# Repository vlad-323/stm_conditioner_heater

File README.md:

# stm_conditioner_heater
 Прилад дозволяє керувати компресором, обігрівом компресора та обігрівом піддона.
 # Схема електрична принципова

 # Зовнішній вигляд приладу

 # Логіка роботи
 1. Ініціалізація усіх входів та виходів
 2. Якщо вхід компресора вимкнений -> компресор і ТЕН компресора вимкнені
 3. work in progress...

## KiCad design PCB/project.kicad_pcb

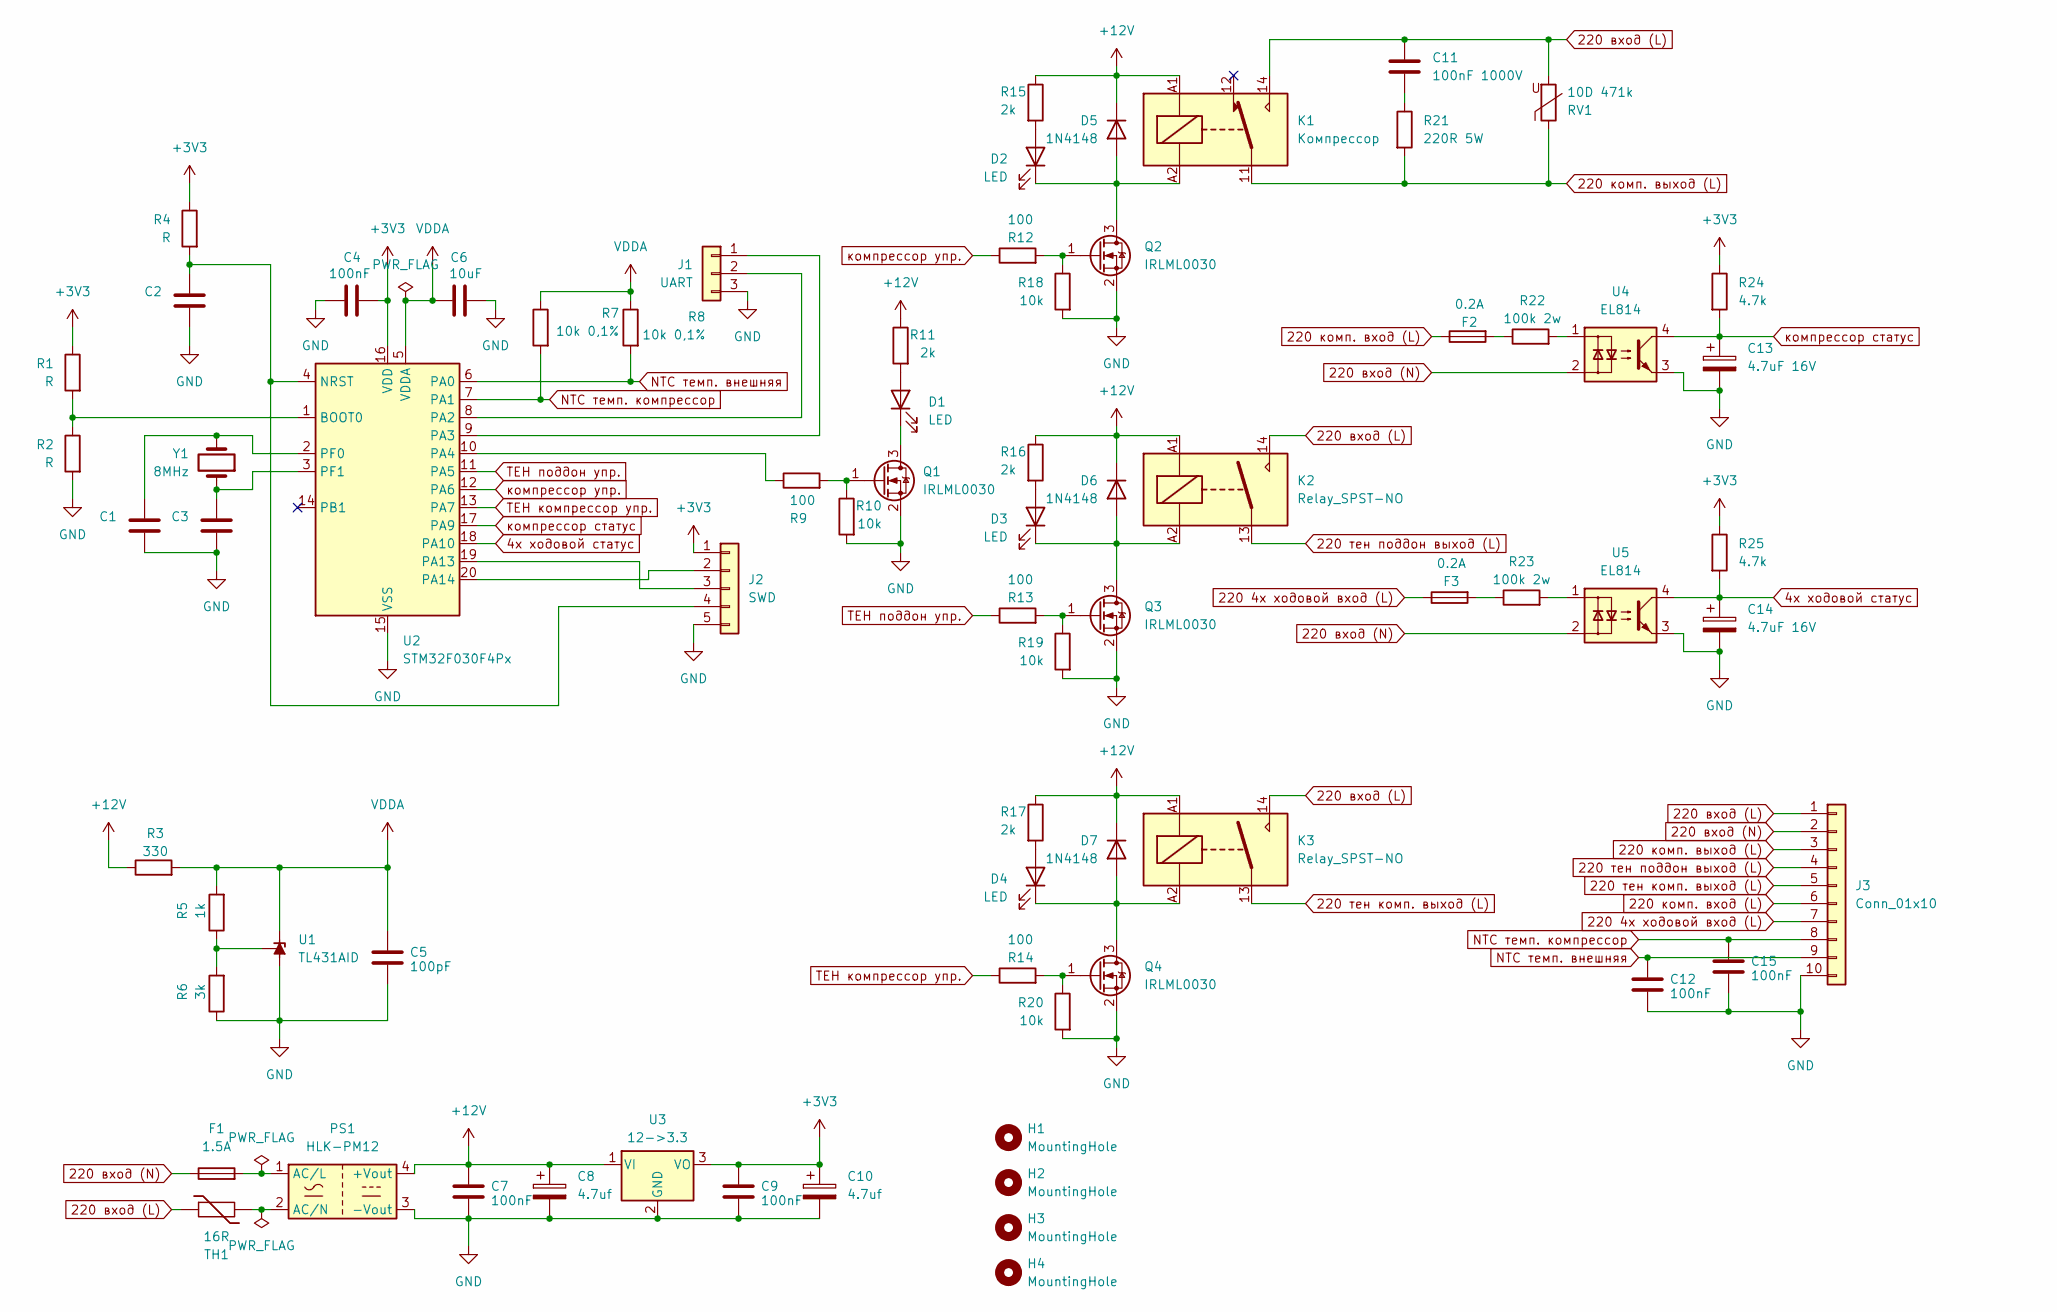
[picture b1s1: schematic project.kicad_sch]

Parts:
C1, C2, C3: C; C_0805_2012Metric_Pad1.18x1.45mm_HandSolder
C4, C7, C9, C12, C15: 100nF; C_0805_2012Metric_Pad1.18x1.45mm_HandSolder
C5: 100pF; C_0805_2012Metric_Pad1.18x1.45mm_HandSolder
C6: 10uF; C_0805_2012Metric_Pad1.18x1.45mm_HandSolder
C8, C10: 4.7uf; CP_Radial_D5.0mm_P2.50mm
C11: 100nF 1000V; C_Axial_L12.0mm_D6.5mm_P15.00mm_Horizontal
C13, C14: 4.7uF 16V; CP_Radial_D5.0mm_P2.00mm
D1, D2, D3, D4: LED; LED_D3.0mm
D5, D6, D7: 1N4148; D_DO-35_SOD27_P7.62mm_Horizontal
F1: 1.5A; Fuse_BelFuse_0ZRE0016FF_L9.9mm_W3.8mm
F2, F3: 0.2A; Fuse_BelFuse_0ZRE0016FF_L9.9mm_W3.8mm
H1, H2, H3, H4: MountingHole; MountingHole_3.2mm_M3
J1: UART; PinHeader_1x03_P2.54mm_Vertical
J2: SWD; PinHeader_1x05_P2.54mm_Vertical
J3: Conn_01x10; PhoenixContact_MSTB_2,5_10-GF-5,08_1x10_P5.08mm_Horizontal_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
K1: Компрессор; Relay_SPDT_RAYEX-L90S
K2, K3: Relay_SPST-NO; Relay_SPST_Schrack-RP-II-1-FormA_RM3.5mm
PS1: HLK-PM12; Converter_ACDC_Hi-Link_HLK-PMxx
Q1, Q2, Q3, Q4: IRLML0030; SOT-23W_Handsoldering
R1, R2, R4: R; R_0805_2012Metric_Pad1.20x1.40mm_HandSolder
R3: 330; R_1206_3216Metric_Pad1.30x1.75mm_HandSolder
R5: 1k; R_1206_3216Metric_Pad1.30x1.75mm_HandSolder
R6: 3k; R_1206_3216Metric_Pad1.30x1.75mm_HandSolder
R7, R8: 10k 0,1%; R_1206_3216Metric_Pad1.30x1.75mm_HandSolder
R9, R12, R13, R14: 100; R_0805_2012Metric_Pad1.20x1.40mm_HandSolder
R10, R18, R19, R20: 10k; R_0805_2012Metric_Pad1.20x1.40mm_HandSolder
R11, R15, R16, R17: 2k; R_0805_2012Metric_Pad1.20x1.40mm_HandSolder
R21: 220R 5W; R_Axial_DIN0918_L18.0mm_D9.0mm_P25.40mm_Horizontal
R22, R23: 100k 2w; R_Axial_DIN0207_L6.3mm_D2.5mm_P5.08mm_Vertical
R24, R25: 4.7k; R_0805_2012Metric_Pad1.20x1.40mm_HandSolder
RV1: 10D 471k; RV_Disc_D9mm_W3.4mm_P5mm
TH1: 16R; R_Axial_DIN0617_L17.0mm_D6.0mm_P7.62mm_Vertical
U1: TL431AID; SOT-23_Handsoldering
U2: STM32F030F4Px; TSSOP-20_4.4x6.5mm_P0.65mm
U3: 12->3.3; TO-220-3_Vertical
U4, U5: EL814; DIP-4_W7.62mm_LongPads
Y1: 8MHz; Crystal_HC18-U_Vertical

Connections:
4х ходовой статус: C14.1, R25.2, U2.18 (PA10), U5.4
220 4х ходовой вход (L): F3.1, J3.7
220 вход (L): C11.1, J3.1, K1.14, K2.14, K3.14, RV1.2, TH1.1
220 вход (N): F1.1, J3.2, U4.2, U5.2
220 комп. вход (L): F2.1, J3.6
220 комп. выход (L): J3.3, K1.11, R21.2, RV1.1
220 тен комп. выход (L): J3.5, K3.13
220 тен поддон выход (L): J3.4, K2.13
+3V3: C4.1, C9.1, C10.1, J2.1, R1.1, R4.1, R24.1, R25.1, U2.16 (VDD), U3.3 (VO)
+12V: C7.1, C8.1, D5.1 (K), D6.1 (K), D7.1 (K), K1.A1, K2.A1, K3.A1, PS1.4 (+Vout), R3.1, R11.1, R15.1, R16.1, R17.1, U3.1 (VI)
GND: C1.2, C2.2, C3.2, C4.2, C5.2, C6.2, C7.2, C8.2, C9.2, C10.2, C12.2, C13.2, C14.2, C15.2, J1.3, J2.5, J3.10, PS1.3 (-Vout), Q1.2 (S), Q2.2 (S), Q3.2 (S), Q4.2 (S), R2.2, R6.1, R10.2, R18.2, R19.2, R20.2, U1.3 (A), U2.15 (VSS), U3.2 (GND), U4.3, U5.3
NTC темп. внешняя: C12.1, J3.9, R8.2, U2.6 (PA0)
NTC темп. компрессор: C15.1, J3.8, R7.2, U2.7 (PA1)
unnamed: C11.2, R21.1
unnamed: D1.2 (A), R11.2
unnamed: D1.1 (K), Q1.3 (D)
unnamed: D2.2 (A), R15.2
unnamed: D2.1 (K), D5.2 (A), K1.A2, Q2.3 (D)
unnamed: D3.2 (A), R16.2
unnamed: D3.1 (K), D6.2 (A), K2.A2, Q3.3 (D)
unnamed: D4.2 (A), R17.2
unnamed: D4.1 (K), D7.2 (A), K3.A2, Q4.3 (D)
unnamed: F2.2, R22.1
unnamed: F3.2, R23.1
unnamed: J1.1, U2.9 (PA3)
unnamed: J1.2, U2.8 (PA2)
unnamed: J2.2, U2.20 (PA14)
unnamed: J2.3, U2.19 (PA13)
unnamed: C2.1, J2.4, R4.2, U2.4 (NRST)
unnamed: F1.2, PS1.1 (AC/L)
unnamed: PS1.2 (AC/N), TH1.2
unnamed: Q1.1 (G), R9.2, R10.1
unnamed: Q2.1 (G), R12.2, R18.1
unnamed: Q3.1 (G), R13.2, R19.1
unnamed: Q4.1 (G), R14.2, R20.1
unnamed: R22.2, U4.1
unnamed: R23.2, U5.1
unnamed: R5.1, R6.2, U1.2 (REF)
unnamed: R1.2, R2.1, U2.1 (BOOT0)
unnamed: R9.1, U2.10 (PA4)
unnamed: C1.1, U2.2 (PF0), Y1.2
unnamed: C3.1, U2.3 (PF1), Y1.1
VDDA: C5.1, C6.1, R3.2, R5.2, R7.1, R8.1, U1.1 (K), U2.5 (VDDA)
ТЕН компрессор упр.: R14.1, U2.13 (PA7)
ТЕН поддон упр.: R13.1, U2.11 (PA5)
компрессор статус: C13.1, R24.2, U2.17 (PA9), U4.4
компрессор упр.: R12.1, U2.12 (PA6)

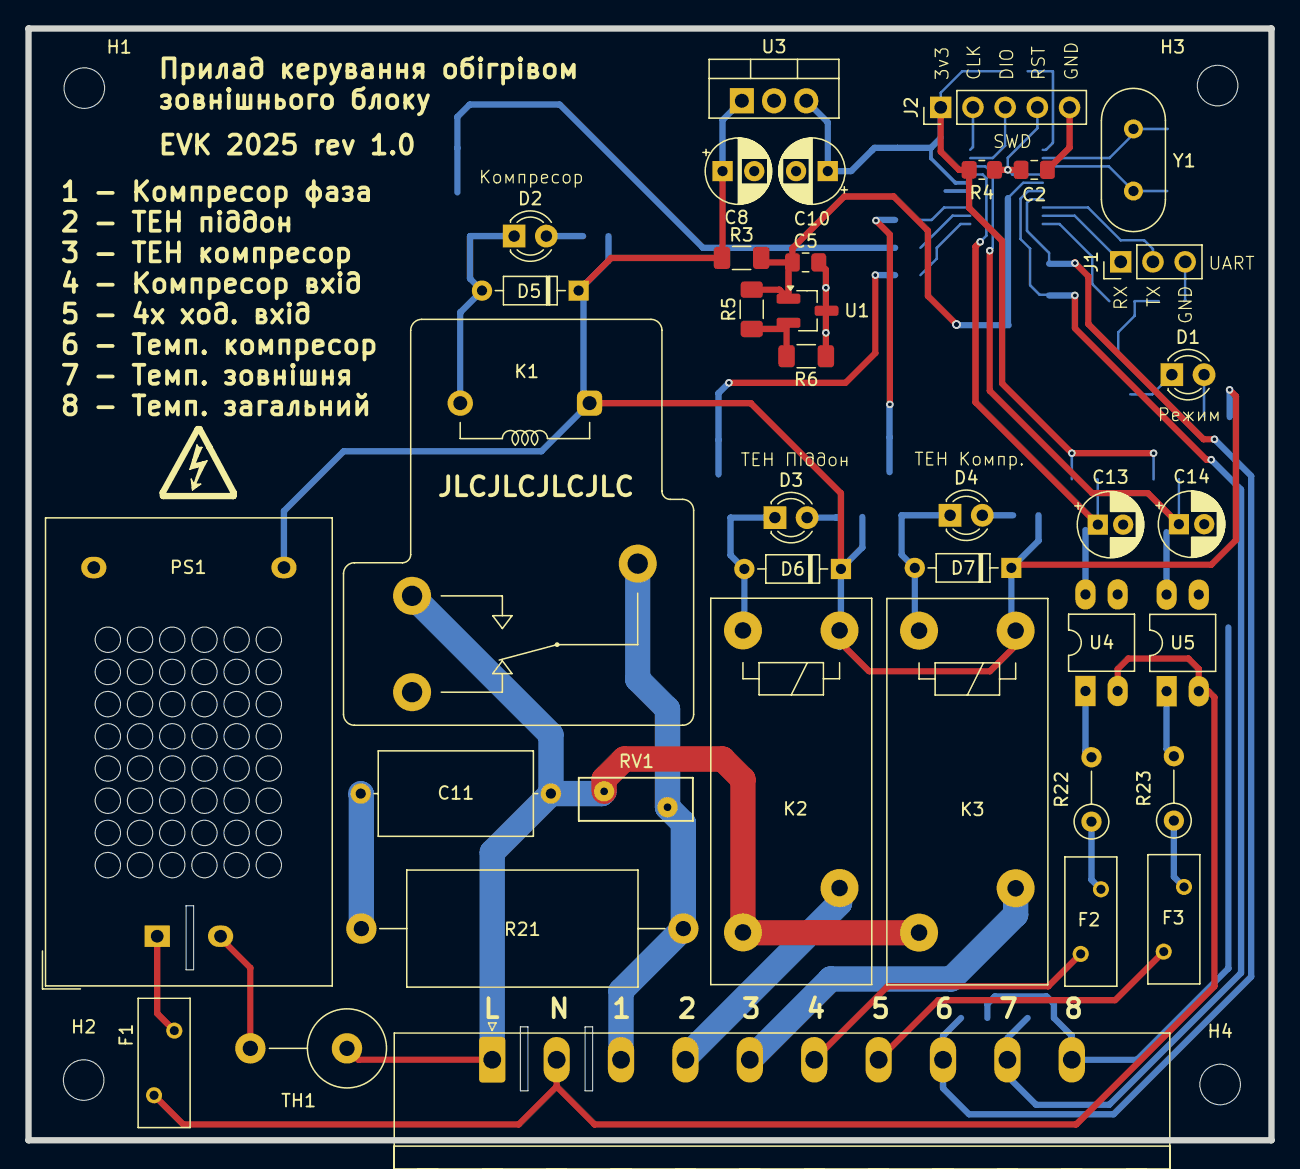
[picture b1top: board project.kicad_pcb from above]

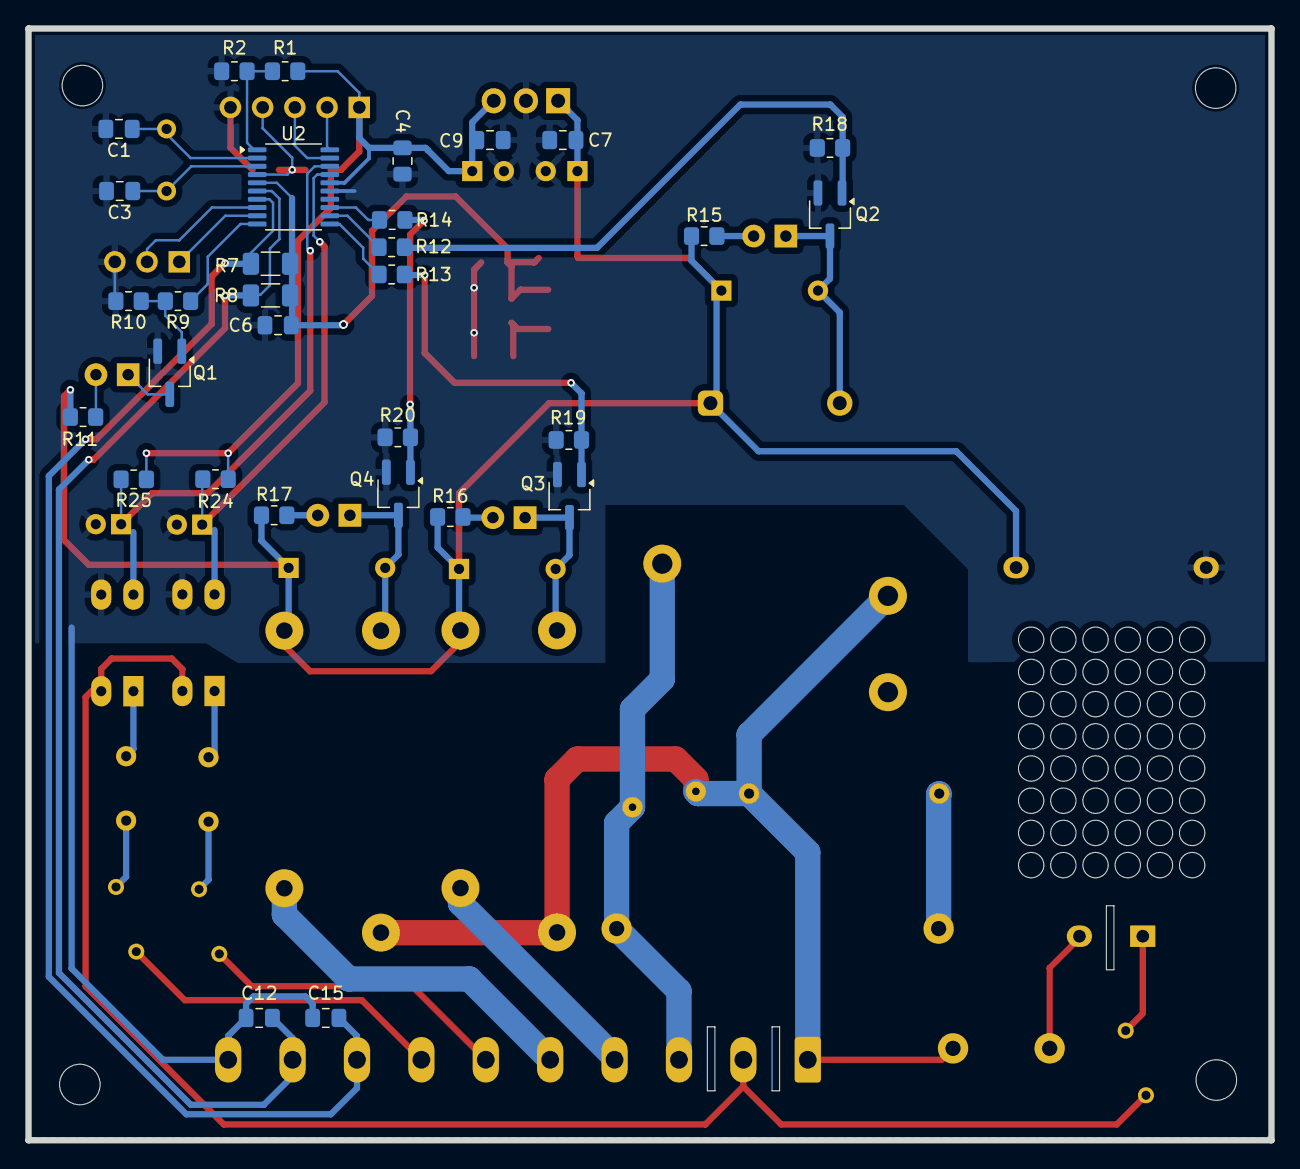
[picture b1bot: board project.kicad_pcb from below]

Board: 2 copper layers, 98.1 x 87.7 mm, 73 parts (31 on the bottom side), 47 nets.

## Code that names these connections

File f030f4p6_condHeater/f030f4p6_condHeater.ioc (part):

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Mcu.Name=STM32F030F4Px
Mcu.Package=TSSOP20
Mcu.UserName=STM32F030F4Px
PA0.GPIOParameters=GPIO_Label
PA0.GPIO_Label=NTC_outside
PA0.Mode=IN0
PA0.Signal=ADC_IN0
PA1.GPIOParameters=GPIO_Label
PA1.GPIO_Label=NTC_compr
PA1.Mode=IN1
PA1.Signal=ADC_IN1
PA10.GPIOParameters=GPIO_Label
PA10.GPIO_Label=Valve_state
PA10.Signal=GPIO_Input
PA13.Mode=Serial_Wire
PA13.Signal=SYS_SWDIO
PA14.Mode=Serial_Wire
PA14.Signal=SYS_SWCLK
PA2.Mode=Asynchronous
PA2.Signal=USART1_TX
PA3.Mode=Asynchronous
PA3.Signal=USART1_RX
PA4.GPIOParameters=GPIO_Label
PA4.GPIO_Label=LED_state
PA4.Signal=GPIO_Output
PA5.GPIOParameters=GPIO_Label
PA5.GPIO_Label=TEN_pallet_ctrl
PA5.Signal=GPIO_Output
PA6.GPIOParameters=GPIO_Label
PA6.GPIO_Label=Compr_ctrl
PA6.Signal=GPIO_Output
PA7.GPIOParameters=GPIO_Label
PA7.GPIO_Label=TEN_compr_ctrl
PA7.Signal=GPIO_Output
PA9.GPIOParameters=GPIO_Label
PA9.GPIO_Label=Compr_state
PA9.Signal=GPIO_Input
PF0-OSC_IN.Mode=HSE-External-Oscillator
PF0-OSC_IN.Signal=RCC_OSC_IN
PF1-OSC_OUT.Mode=HSE-External-Oscillator
PF1-OSC_OUT.Signal=RCC_OSC_OUT
RCC.SYSCLKSource=RCC_SYSCLKSOURCE_HSE
board=custom

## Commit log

2024-11-16 Updated schematic(not finished)
2024-11-17 Updated PCB (still not finished)
2024-12-30 PCB and schematic done
2025-01-26 Updated PCB
2025-01-26 Firmware (not finished, not full tested)
2025-04-15 Added case
2025-04-15 added schematic
